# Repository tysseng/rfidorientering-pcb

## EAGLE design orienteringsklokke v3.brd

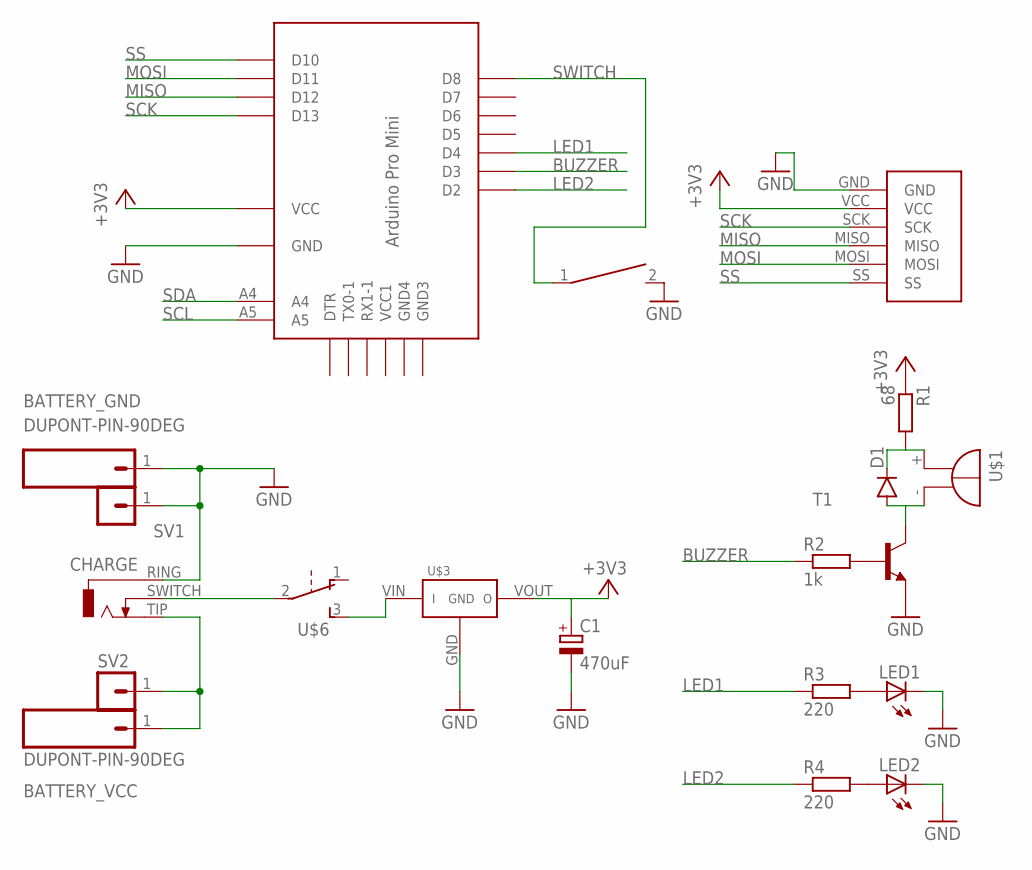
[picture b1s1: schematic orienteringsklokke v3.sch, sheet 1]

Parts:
BATTERY_GND: DUPONT-PIN-90DEG
BATTERY_VCC: DUPONT-PIN-90DEG
C1: 470uF; CAP-HORIZ-6.5X11X2.5
CHARGE: ST613-JACK
D1: 1N4148DOJ35-5; DO35-5J
LED1, LED2: LED_J3MM-LEFT; LED90DEG_LEFT
R1: 68; 0204/5
R2: 1k; 0204/5
R3, R4: 220; 0204/5
SV1, SV2: MA01-1JC; MA01-1J
T1: 2N3904-NPN-TO92-EBC; TO92-EBC
U$1: BUZZER_JL; BUZZER_HORIZ_J_LEFT
U$2: NFC_MODULE_V3_SPINH; NFC_MODULE_V3_SPI_CENTERED_NO_HOLES
U$3: VOLT_BOOST; VOLT-BOOST
U$4: ARD-PRO-MINI-ORIENTERING; ARD_PRO_MINI_ORIENTERING
U$5: PUSHBUTTON_2P6MM; PUSHBUTTON_HORIZ_6MM_J
U$6: SK12D07-SLIDE-SWITCH; SK12D07

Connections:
+3V3: C1.+, R1.1, U$2.VCC, U$3.VOUT, U$4.VCC
BUZZER: R2.1, U$4.D3
GND: BATTERY_GND.1, C1.-, CHARGE.RING (1), LED1.K (C), LED2.K (C), SV1.1, T1.E, U$2.GND, U$3.GND, U$4.GND, U$5.2
LED1: R3.1, U$4.D4
LED2: R4.1, U$4.D2
MISO: U$2.MISO, U$4.D12
MOSI: U$2.MOSI, U$4.D11
unnamed: CHARGE.SWITCH (2), U$6.2
unnamed: D1.A, T1.C, U$1.-
unnamed: R2.2, T1.B
unnamed: D1.C, R1.2, U$1.+
unnamed: LED1.A, R3.2
unnamed: BATTERY_VCC.1, CHARGE.TIP (3), SV2.1
unnamed: U$3.VIN, U$6.3
unnamed: LED2.A, R4.2
SCK: U$2.SCK, U$4.D13
SCL: U$4.A5
SDA: U$4.A4
SS: U$2.SS, U$4.D10
SWITCH: U$4.D8, U$5.1

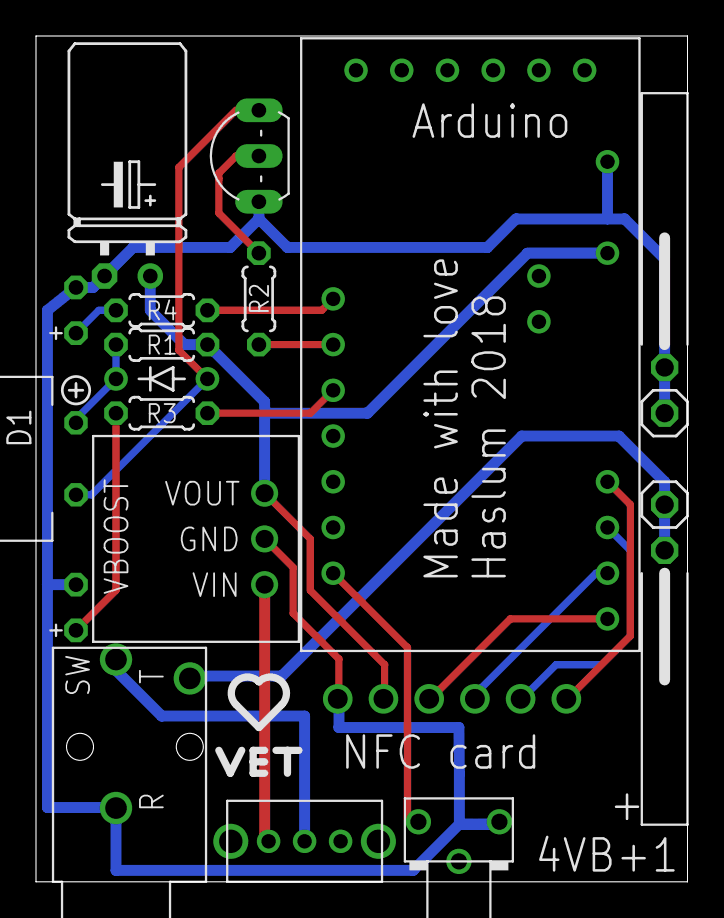
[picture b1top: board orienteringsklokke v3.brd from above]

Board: 2 copper layers, 36.2 x 47.0 mm, 20 parts (0 on the bottom side), 18 nets.

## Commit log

2018-10-07 Orienteringsklokke PCB
2018-10-07 Fully traced with jack, switch, buzzer and no battery box
2018-10-13 Rotated battery 90 degrees, working on case layout
2018-10-15 Lots of work on version 3
2018-10-27 Hopefully final layout, tracing left
2018-10-27 Traced and fixed most silk screening
2018-10-27 4VB+1 etc
